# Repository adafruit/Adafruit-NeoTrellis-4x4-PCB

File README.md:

## Adafruit NeoTrellis RGB Driver PCB for 4x4 Keypad PCB

<a href="http://www.adafruit.com/products/3954"><br/>
Click here to purchase one from the Adafruit shop</a>

PCB files for the Adafruit NeoTrellis RGB Driver PCB for 4x4 Keypad. Format is EagleCAD schematic and board layout
* https://www.adafruit.com/product/3954

### Description

By popular request, we've upgraded our popular Trellis elastomer button kits to now have a PCB with full color NeoPixel support! You heard that right, no more single-color LEDs, you can now have any color you like under the fantastic rubbery button pads we sell.

These 4x4 button pad boards are fully tile-able and communicate over I2C. With 5 address pins, you've got the ability to connect up to 32 together in any arrangement you like. [With our trusty seesaw I2C-to-anything chip](https://learn.adafruit.com/adafruit-seesaw-atsamd09-breakout), you don't even need to manage the NeoPixel driving. That's right! Both the button management and LED driving is completely handled for you all over plain I2C. With both Arduino/C++ and CircuitPython/Python library support, you can use these pads with any and all microcontroller or computer boards.

Perfect for your next cool interface, MIDI instrument, control panel...whatever could benefit from beautiful diffused colorful buttons. For fast connection to a single board, we include a JST-PH 4-pin connector that will give you power+data access. It's Grove compatible (the cable fits, even though its not the exact same connector), [or you can use a JST-PH 4 pin cable](https://www.adafruit.com/product/3568).

**You can tile up to 32 boards together by soldering them edge-to-edge and soldering closed the I2C address jumpers, then use one I2C connection for all tiled NeoTrellis boards!**

Each order comes with one NeoTrellis board with seesaw chip and 16 NeoPixels already soldered in place. **Elastomer button pad not included**, [so be sure to pick one up!](https://www.adafruit.com/product/1611)

### License

Adafruit invests time and resources providing this open source design, please support Adafruit and open-source hardware by purchasing products from [Adafruit](https://www.adafruit.com)!

Designed by Limor Fried/Ladyada for Adafruit Industries.

Creative Commons Attribution/Share-Alike, all text above must be included in any redistribution. See license.txt for additional details.

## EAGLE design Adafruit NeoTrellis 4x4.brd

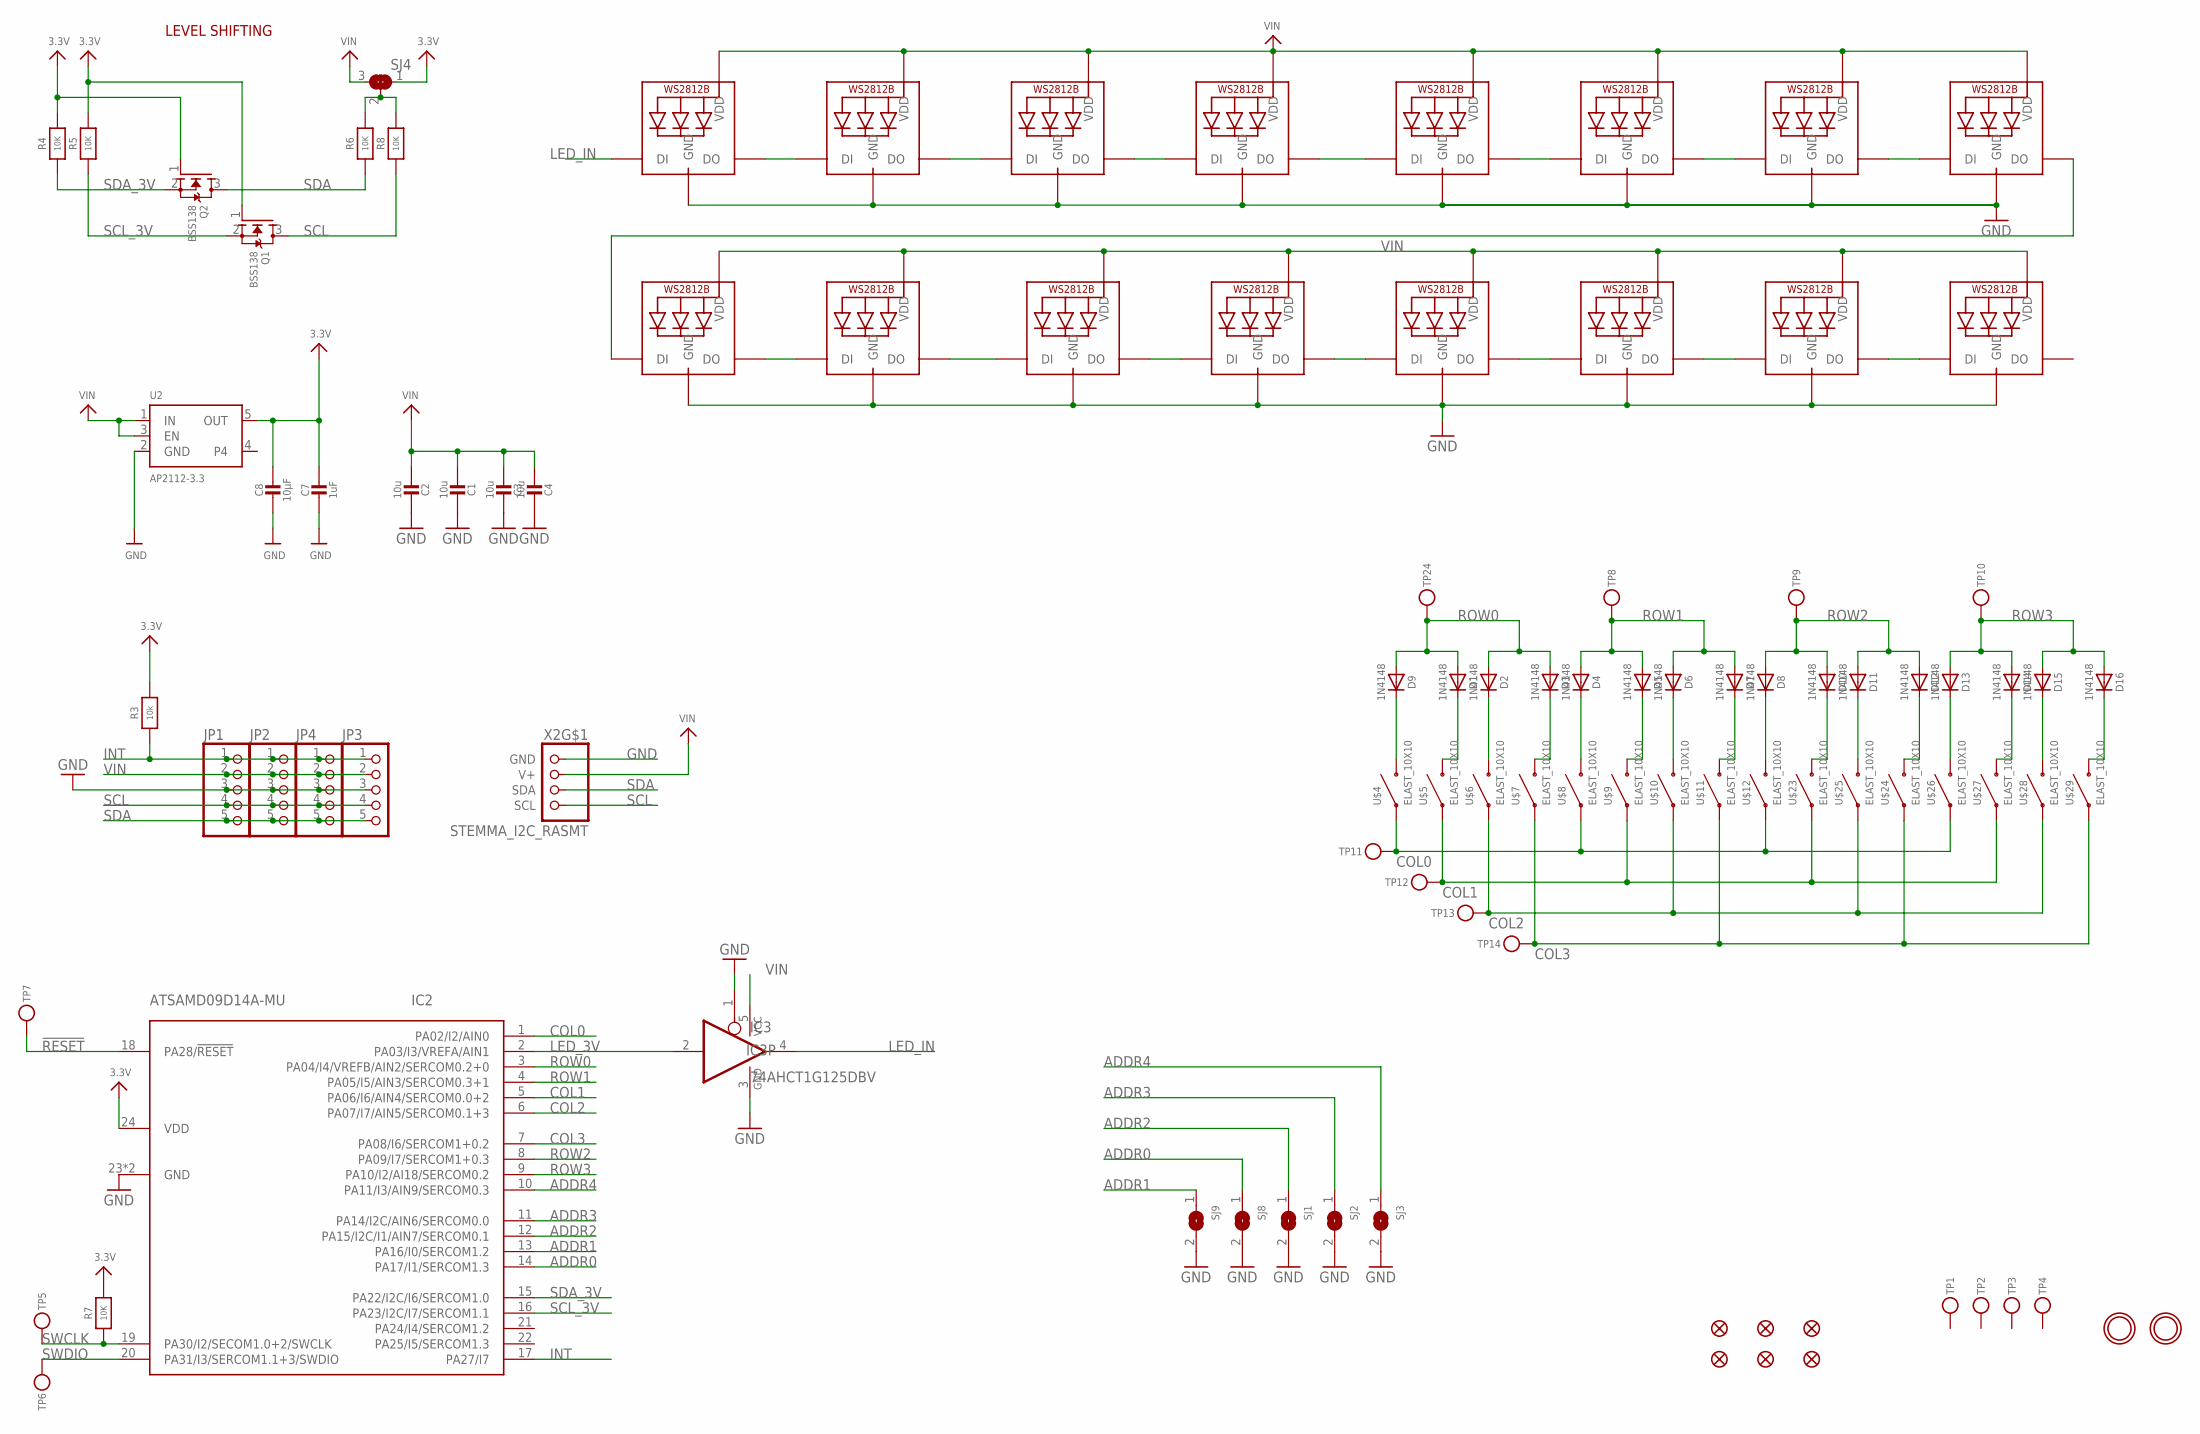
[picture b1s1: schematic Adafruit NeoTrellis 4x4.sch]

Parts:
C1, C2, C3, C4: 10u; 0805-NO
C7: 1uF; 0603-NO
C8: 10µF; 0805-NO
D1, D2, D3, D4, D5, D6, D7, D8, D9, D10, D11, D12, D13, D14, D15, D16: 1N4148; SOD-323
FID1, FID2, FID3, FID4, FID5, FID6: FIDUCIAL_1MM
IC2: ATSAMD09D14A-MU; QFN24_4MM
IC3: 74AHCT1G125DBV; SOT23-5
JP1, JP2, JP3, JP4: HEADER-1X5EDGESMT; 5P_EDGECONNECT
LED1, LED2, LED3, LED4, LED5, LED6, LED7, LED8, LED9, LED10, LED11, LED12, LED13, LED14, LED15, LED16: WS2812B3535; LED3535
Q1, Q2: BSS138; SOT23-WIDE
R3: 10k; 0603-NO
R4, R5, R6, R7, R8: 10K; 0603-NO
SJ1, SJ2, SJ3, SJ8, SJ9: SOLDERJUMPER; SOLDERJUMPER_ARROW_NOPASTE
SJ4: SOLDERJUMPER_2WAY; SOLDERJUMPER_2WAY_OPEN_NOPASTE
TP1, TP2, TP3, TP4: TESTPOINT; TESTPOINT_SMT
TP5, TP6: TESTPOINTROUND2MM; TESTPOINT_ROUND_2MM
TP7, TP8, TP9, TP10, TP11, TP12, TP13, TP14, TP24: TESTPOINTROUND1.5MM; TESTPOINT_ROUND_1.5MM
U2: AP2112-3.3; SOT23-5
U$1, U$2: MOUNTINGHOLE2.5; MOUNTINGHOLE_2.5_PLATED
U$4, U$5, U$6, U$7, U$8, U$9, U$10, U$11, U$12, U$23, U$24, U$25, U$26, U$27, U$28, U$29: ELAST_10X10; ELAST_PAD_SQUARE_10MM_4X4WIDE
X2: STEMMA_I2C_RASMT; JSTPH4

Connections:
3.3V: C7.1, C8.1, IC2.24 (VDD), Q1.1 (G), Q2.1 (G), R3.2, R4.2, R5.2, R7.2, SJ4.1, U2.5 (OUT)
!RESET: IC2.18 (PA28/!RESET), TP7.P$1
ADDR0: IC2.14 (PA17/I1/SERCOM1.3), SJ8.1
ADDR1: IC2.13 (PA16/I0/SERCOM1.2), SJ9.1
ADDR2: IC2.12 (PA15/I2C/I1/AIN7/SERCOM0.1), SJ1.1
ADDR3: IC2.11 (PA14/I2C/AIN6/SERCOM0.0), SJ2.1
ADDR4: IC2.10 (PA11/I3/AIN9/SERCOM0.3), SJ3.1
COL0: IC2.1 (PA02/I2/AIN0), TP11.P$1, U$4.P$1, U$8.P$1, U$12.P$1, U$26.P$1
COL1: IC2.5 (PA06/I6/AIN4/SERCOM0.0+2), TP12.P$1, U$5.P$1, U$9.P$1, U$23.P$1, U$27.P$1
COL2: IC2.6 (PA07/I7/AIN5/SERCOM0.1+3), TP13.P$1, U$6.P$1, U$10.P$1, U$25.P$1, U$28.P$1
COL3: IC2.7 (PA08/I6/SERCOM1+0.2), TP14.P$1, U$7.P$1, U$11.P$1, U$24.P$1, U$29.P$1
GND: C1.1, C2.1, C3.1, C4.1, C7.2, C8.2, IC2.23 (GND), IC2.THERM (GND), IC3.1 (OE), IC3.3 (GND), JP1.3, JP2.3, JP3.3, JP4.3, LED1.4 (GND), LED2.4 (GND), LED3.4 (GND), LED4.4 (GND), LED5.4 (GND), LED6.4 (GND), LED7.4 (GND), LED8.4 (GND), LED9.4 (GND), LED10.4 (GND), LED11.4 (GND), LED12.4 (GND), LED13.4 (GND), LED14.4 (GND), LED15.4 (GND), LED16.4 (GND), SJ1.2, SJ2.2, SJ3.2, SJ8.2, SJ9.2, U2.2 (GND), X2.1 (GND)
INT: IC2.17 (PA27/I7), JP1.1, JP2.1, JP3.1, JP4.1, R3.1
LED_3V: IC2.2 (PA03/I3/VREFA/AIN1), IC3.2 (I)
LED_IN: IC3.4 (O), LED1.1 (DI)
unnamed: R6.2, R8.2, SJ4.2
unnamed: D9.C, U$4.P$2
unnamed: D1.C, U$5.P$2
unnamed: D2.C, U$6.P$2
unnamed: D3.C, U$7.P$2
unnamed: D4.C, U$8.P$2
unnamed: D5.C, U$9.P$2
unnamed: LED1.3 (DO), LED2.1 (DI)
unnamed: LED2.3 (DO), LED3.1 (DI)
unnamed: LED3.3 (DO), LED4.1 (DI)
unnamed: LED4.3 (DO), LED5.1 (DI)
unnamed: D6.C, U$10.P$2
unnamed: LED5.3 (DO), LED6.1 (DI)
unnamed: LED6.3 (DO), LED7.1 (DI)
unnamed: D7.C, U$11.P$2
unnamed: LED7.3 (DO), LED8.1 (DI)
unnamed: D8.C, U$12.P$2
unnamed: LED8.3 (DO), LED9.1 (DI)
unnamed: D10.C, U$23.P$2
unnamed: D11.C, U$25.P$2
unnamed: D12.C, U$24.P$2
unnamed: D13.C, U$26.P$2
unnamed: D14.C, U$27.P$2
unnamed: D15.C, U$28.P$2
unnamed: D16.C, U$29.P$2
unnamed: LED9.3 (DO), LED10.1 (DI)
unnamed: LED10.3 (DO), LED12.1 (DI)
unnamed: LED11.1 (DI), LED12.3 (DO)
unnamed: LED11.3 (DO), LED13.1 (DI)
unnamed: LED13.3 (DO), LED14.1 (DI)
unnamed: LED14.3 (DO), LED15.1 (DI)
unnamed: LED15.3 (DO), LED16.1 (DI)
ROW0: D1.A, D2.A, D3.A, D9.A, IC2.3 (PA04/I4/VREFB/AIN2/SERCOM0.2+0), TP24.P$1
ROW1: D4.A, D5.A, D6.A, D7.A, IC2.4 (PA05/I5/AIN3/SERCOM0.3+1), TP8.P$1
ROW2: D8.A, D10.A, D11.A, D12.A, IC2.8 (PA09/I7/SERCOM1+0.3), TP9.P$1
ROW3: D13.A, D14.A, D15.A, D16.A, IC2.9 (PA10/I2/AI18/SERCOM0.2), TP10.P$1
SCL: JP1.4, JP2.4, JP3.4, JP4.4, Q1.3 (D), R8.1, X2.4 (SCL)
SCL_3V: IC2.16 (PA23/I2C/I7/SERCOM1.1), Q1.2 (S), R5.1
SDA: JP1.5, JP2.5, JP3.5, JP4.5, Q2.3 (D), R6.1, X2.3 (SDA)
SDA_3V: IC2.15 (PA22/I2C/I6/SERCOM1.0), Q2.2 (S), R4.1
SWCLK: IC2.19 (PA30/I2/SECOM1.0+2/SWCLK), R7.1, TP5.P$1
SWDIO: IC2.20 (PA31/I3/SERCOM1.1+3/SWDIO), TP6.P$1
VIN: C1.2, C2.2, C3.2, C4.2, IC3.5 (VCC), JP1.2, JP2.2, JP3.2, JP4.2, LED1.2 (VDD), LED2.2 (VDD), LED3.2 (VDD), LED4.2 (VDD), LED5.2 (VDD), LED6.2 (VDD), LED7.2 (VDD), LED8.2 (VDD), LED9.2 (VDD), LED10.2 (VDD), LED11.2 (VDD), LED12.2 (VDD), LED13.2 (VDD), LED14.2 (VDD), LED15.2 (VDD), LED16.2 (VDD), SJ4.3, U2.1 (IN), U2.3 (EN), X2.2 (V+)

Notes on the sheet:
LEVEL SHIFTING

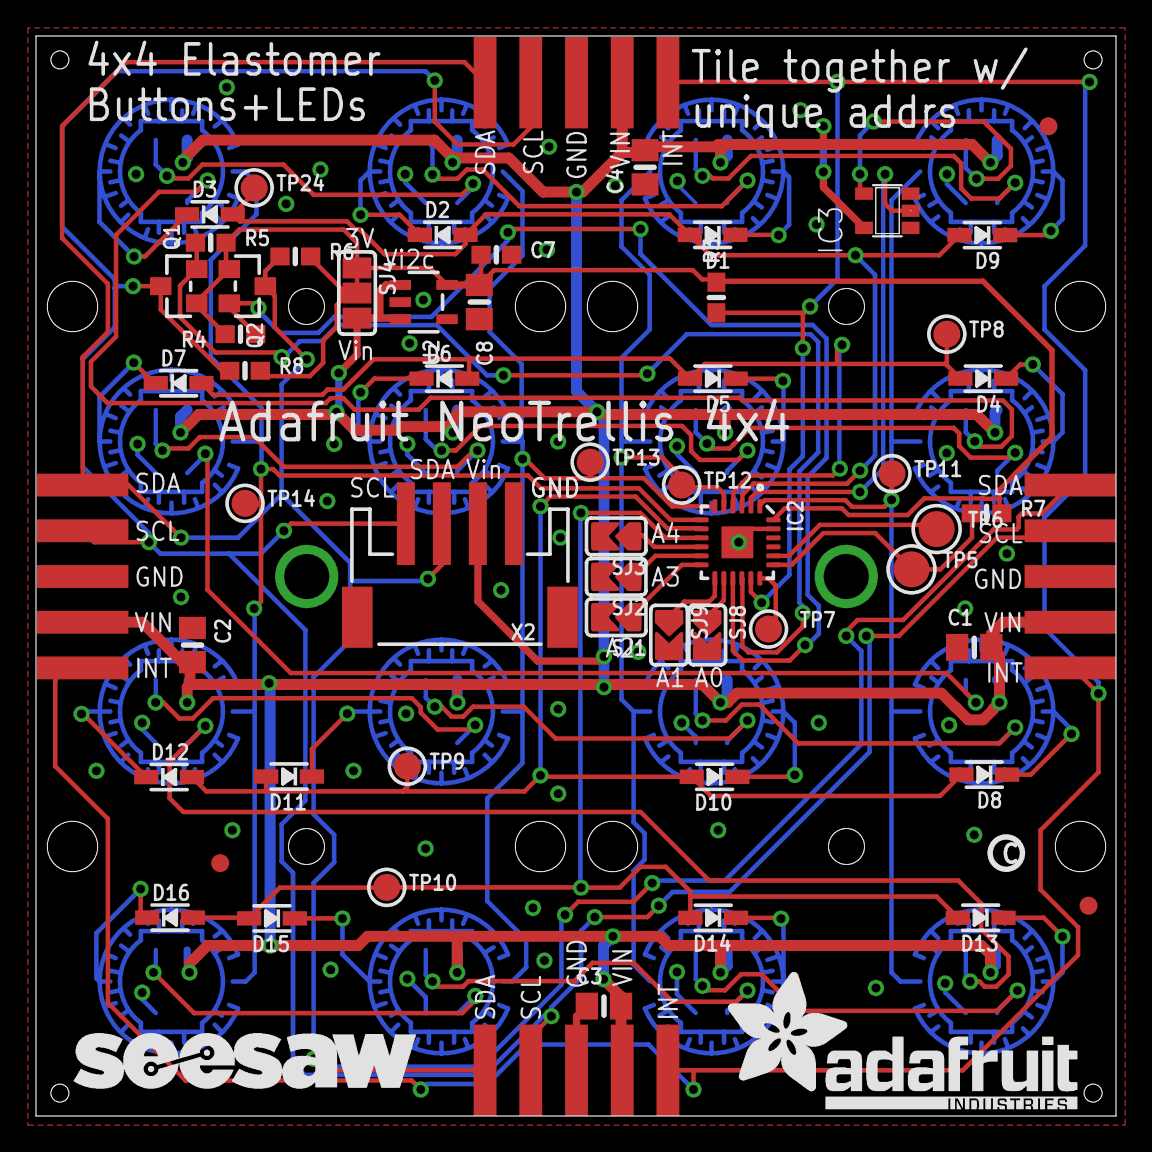
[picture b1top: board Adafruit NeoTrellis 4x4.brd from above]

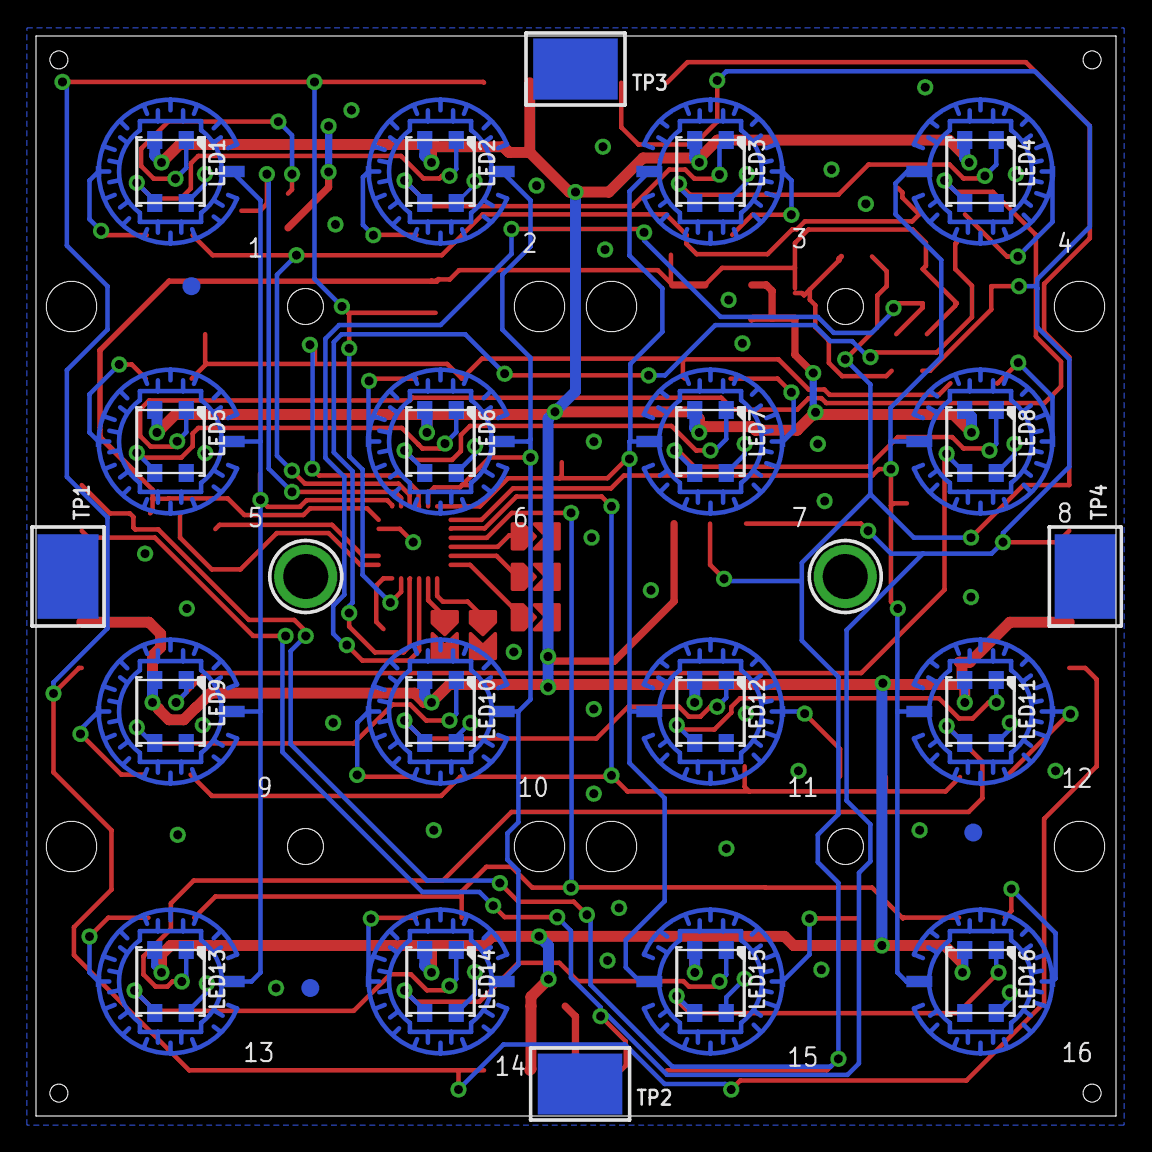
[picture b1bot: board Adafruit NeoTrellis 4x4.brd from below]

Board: 2 copper layers, 60.0 x 60.0 mm, 102 parts (41 on the bottom side), 58 nets.

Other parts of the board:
U$3: ADAFRUIT_TEXT_20MM
U$14: SEESAW_LOGO
U$19: PCBFEAT-REV-040

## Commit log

2018-09-19 init
2019-07-16 updated to use the new cookiecutter for pcb repos

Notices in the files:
parts and their libraries:
microbuilder: This work is placed in the public domain, and may be freely used for commercial and non-commercial work with the following conditions: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
